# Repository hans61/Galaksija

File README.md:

# Galaksija Plus

I became aware of the "Galaksija" in this forum:

https://forum.classic-computing.de/forum/index.php?thread/27005-nachbau-eines-galaksija-plus-computers/&postID=372260#post372260

I find the Yugoslavian computer from 1983 based on a Z80 very interesting. Especially the idea to give it a SD card afterwards. Especially since it does not use a microcontroller, but implements the SPI interface with a 74LS299.

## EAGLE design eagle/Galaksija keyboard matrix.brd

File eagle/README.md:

# Galaksija keyboard matrix

My attempt to design a PCB for a keyboard of a Galaksija Plus.
Currently it is still untested!

For the first attempt I decided to use 12mm x 12mm styli.
Similar to the buttons here:

https://www.mouser.de/ProductDetail/CUI-Devices/TS13-1212-73-BK-100-D?qs=t7xnP681wgVrw7zKuc8u2g%3D%3D

with keycaps similar to these:

https://www.mouser.de/ProductDetail/Mountain-Switch/101-0110-EV?qs=eB3zOl243QFujTA3cWnhpg%3D%3D

My push buttons are from Aliexpress, something like this:

50PCS b3f-4055 12X1 2x 7,3mm 4PIN dip TACT push button schalter Micro key power tactile switches 12x1 2x 7,3 12*12*7,3 MM Licht touc
https://de.aliexpress.com/item/32853348805.html

https://de.aliexpress.com/item/32852734000.html

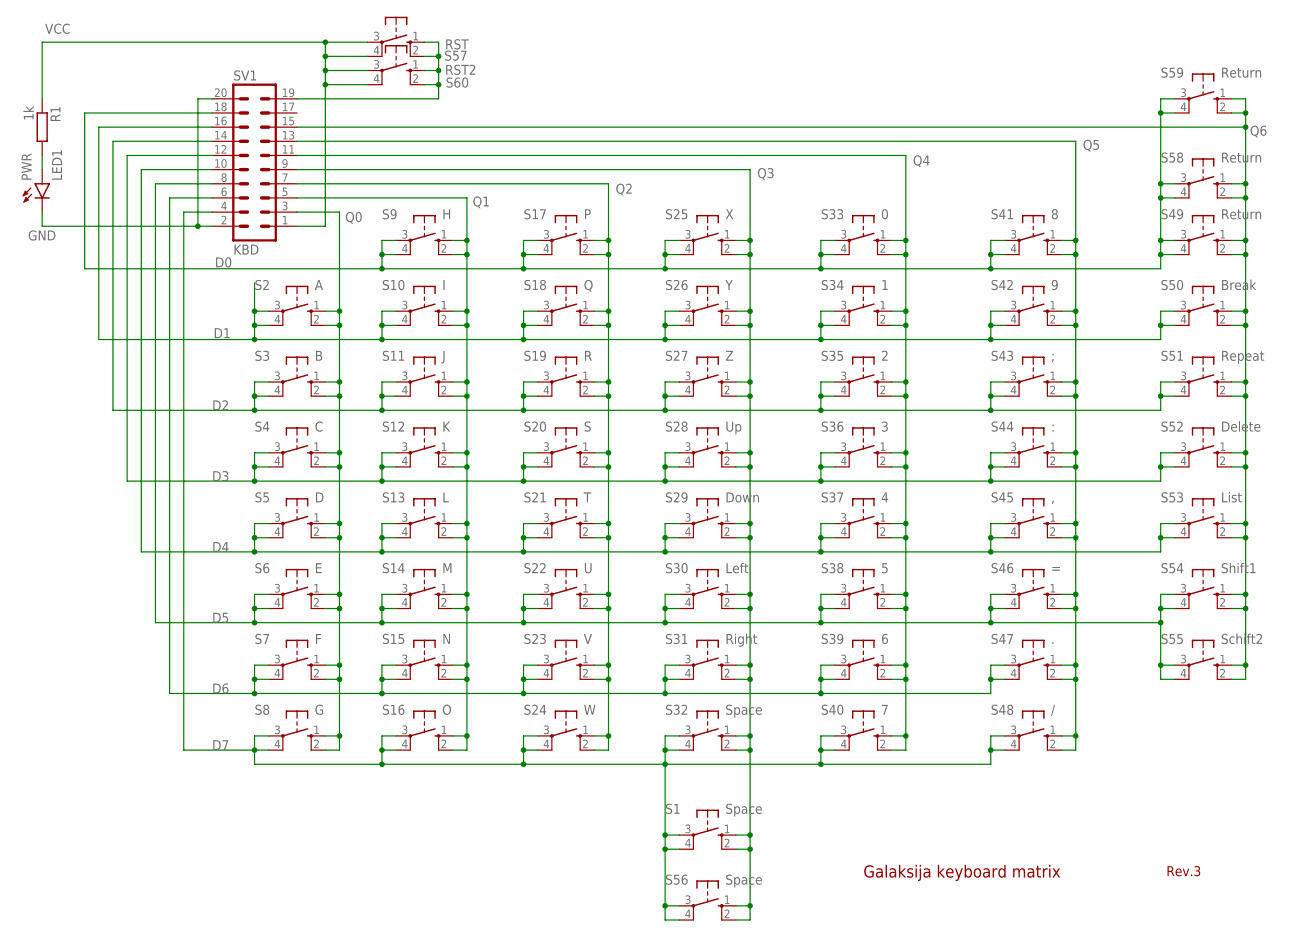
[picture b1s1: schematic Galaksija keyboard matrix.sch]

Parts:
LED1: PWR; LED5MM
R1: 1k; 0207/10
S1, S32, S56: Space; B3F-40XX
S2: A; B3F-40XX
S3: B; B3F-40XX
S4: C; B3F-40XX
S5: D; B3F-40XX
S6: E; B3F-40XX
S7: F; B3F-40XX
S8: G; B3F-40XX
S9: H; B3F-40XX
S10: I; B3F-40XX
S11: J; B3F-40XX
S12: K; B3F-40XX
S13: L; B3F-40XX
S14: M; B3F-40XX
S15: N; B3F-40XX
S16: O; B3F-40XX
S17: P; B3F-40XX
S18: Q; B3F-40XX
S19: R; B3F-40XX
S20: S; B3F-40XX
S21: T; B3F-40XX
S22: U; B3F-40XX
S23: V; B3F-40XX
S24: W; B3F-40XX
S25: X; B3F-40XX
S26: Y; B3F-40XX
S27: Z; B3F-40XX
S28: Up; B3F-40XX
S29: Down; B3F-40XX
S30: Left; B3F-40XX
S31: Right; B3F-40XX
S33: 0; B3F-40XX
S34: 1; B3F-40XX
S35: 2; B3F-40XX
S36: 3; B3F-40XX
S37: 4; B3F-40XX
S38: 5; B3F-40XX
S39: 6; B3F-40XX
S40: 7; B3F-40XX
S41: 8; B3F-40XX
S42: 9; B3F-40XX
S43: ;; B3F-40XX
S44: :; B3F-40XX
S45: ,; B3F-40XX
S46: =; B3F-40XX
S47: .; B3F-40XX
S48: /; B3F-40XX
S49, S58, S59: Return; B3F-40XX
S50: Break; B3F-40XX
S51: Repeat; B3F-40XX
S52: Delete; B3F-40XX
S53: List; B3F-40XX
S54: Shift1; B3F-40XX
S55: Schift2; B3F-40XX
S57: RST; B3F-40XX
S60: RST2; B3F-10XX
SV1: KBD; ML20

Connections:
D0: S9.3, S9.4 (P1), S17.3, S17.4 (P1), S25.3, S25.4 (P1), S33.3, S33.4 (P1), S41.3, S41.4 (P1), S49.3, S49.4 (P1), S58.3, S58.4 (P1), S59.3, S59.4 (P1), SV1.18
D1: S2.3, S2.4 (P1), S10.3, S10.4 (P1), S18.3, S18.4 (P1), S26.3, S26.4 (P1), S34.3, S34.4 (P1), S42.3, S42.4 (P1), S50.3, S50.4 (P1), SV1.16
D2: S3.3, S3.4 (P1), S11.3, S11.4 (P1), S19.3, S19.4 (P1), S27.3, S27.4 (P1), S35.3, S35.4 (P1), S43.3, S43.4 (P1), S51.3, S51.4 (P1), SV1.14
D3: S4.3, S4.4 (P1), S12.3, S12.4 (P1), S20.3, S20.4 (P1), S28.3, S28.4 (P1), S36.3, S36.4 (P1), S44.3, S44.4 (P1), S52.3, S52.4 (P1), SV1.12
D4: S5.3, S5.4 (P1), S13.3, S13.4 (P1), S21.3, S21.4 (P1), S29.3, S29.4 (P1), S37.3, S37.4 (P1), S45.3, S45.4 (P1), S53.3, S53.4 (P1), SV1.10
D5: S6.3, S6.4 (P1), S14.3, S14.4 (P1), S22.3, S22.4 (P1), S30.3, S30.4 (P1), S38.3, S38.4 (P1), S46.3, S46.4 (P1), S54.3, S54.4 (P1), S55.3, S55.4 (P1), SV1.8
D6: S7.3, S7.4 (P1), S15.3, S15.4 (P1), S23.3, S23.4 (P1), S31.3, S31.4 (P1), S39.3, S39.4 (P1), S47.3, S47.4 (P1), SV1.6
D7: S1.3, S1.4 (P1), S8.3, S8.4 (P1), S16.3, S16.4 (P1), S24.3, S24.4 (P1), S32.3, S32.4 (P1), S40.3, S40.4 (P1), S48.3, S48.4 (P1), S56.3, S56.4 (P1), SV1.4
GND: LED1.K (C), SV1.2, SV1.20
unnamed: LED1.A, R1.2
Q0: S2.1 (S), S2.2 (S1), S3.1 (S), S3.2 (S1), S4.1 (S), S4.2 (S1), S5.1 (S), S5.2 (S1), S6.1 (S), S6.2 (S1), S7.1 (S), S7.2 (S1), S8.1 (S), S8.2 (S1), SV1.3
Q1: S9.1 (S), S9.2 (S1), S10.1 (S), S10.2 (S1), S11.1 (S), S11.2 (S1), S12.1 (S), S12.2 (S1), S13.1 (S), S13.2 (S1), S14.1 (S), S14.2 (S1), S15.1 (S), S15.2 (S1), S16.1 (S), S16.2 (S1), SV1.5
Q2: S17.1 (S), S17.2 (S1), S18.1 (S), S18.2 (S1), S19.1 (S), S19.2 (S1), S20.1 (S), S20.2 (S1), S21.1 (S), S21.2 (S1), S22.1 (S), S22.2 (S1), S23.1 (S), S23.2 (S1), S24.1 (S), S24.2 (S1), SV1.7
Q3: S1.1 (S), S1.2 (S1), S25.1 (S), S25.2 (S1), S26.1 (S), S26.2 (S1), S27.1 (S), S27.2 (S1), S28.1 (S), S28.2 (S1), S29.1 (S), S29.2 (S1), S30.1 (S), S30.2 (S1), S31.1 (S), S31.2 (S1), S32.1 (S), S32.2 (S1), S56.1 (S), S56.2 (S1), SV1.9
Q4: S33.1 (S), S33.2 (S1), S34.1 (S), S34.2 (S1), S35.1 (S), S35.2 (S1), S36.1 (S), S36.2 (S1), S37.1 (S), S37.2 (S1), S38.1 (S), S38.2 (S1), S39.1 (S), S39.2 (S1), S40.1 (S), S40.2 (S1), SV1.11
Q5: S41.1 (S), S41.2 (S1), S42.1 (S), S42.2 (S1), S43.1 (S), S43.2 (S1), S44.1 (S), S44.2 (S1), S45.1 (S), S45.2 (S1), S46.1 (S), S46.2 (S1), S47.1 (S), S47.2 (S1), S48.1 (S), S48.2 (S1), SV1.13
Q6: S49.1 (S), S49.2 (S1), S50.1 (S), S50.2 (S1), S51.1 (S), S51.2 (S1), S52.1 (S), S52.2 (S1), S53.1 (S), S53.2 (S1), S54.1 (S), S54.2 (S1), S55.1 (S), S55.2 (S1), S58.1 (S), S58.2 (S1), S59.1 (S), S59.2 (S1), SV1.15
RST: S57.1 (S), S57.2 (S1), S60.1 (S), S60.2 (S1), SV1.19
VCC: R1.1, S57.3, S57.4 (P1), S60.3, S60.4 (P1), SV1.1

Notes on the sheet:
Galaksija keyboard matrix
Rev.3

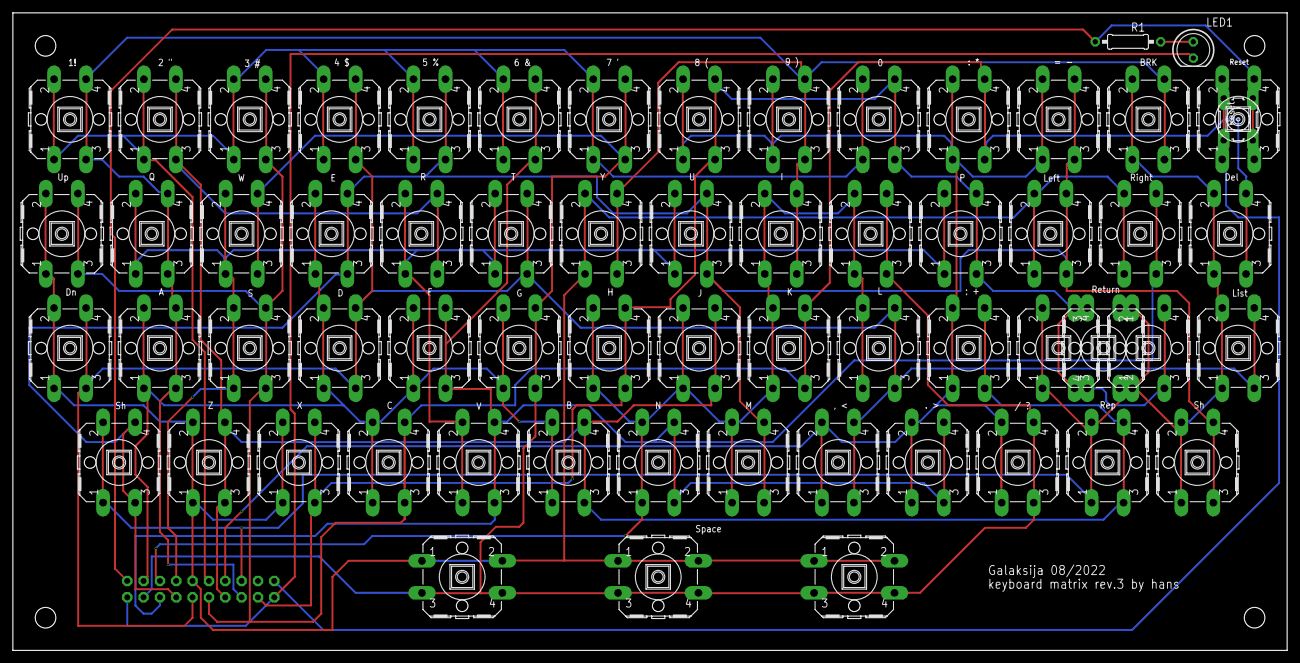
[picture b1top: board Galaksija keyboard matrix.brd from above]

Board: 2 copper layers, 198.1 x 99.1 mm, 63 parts (1 on the bottom side), 19 nets.

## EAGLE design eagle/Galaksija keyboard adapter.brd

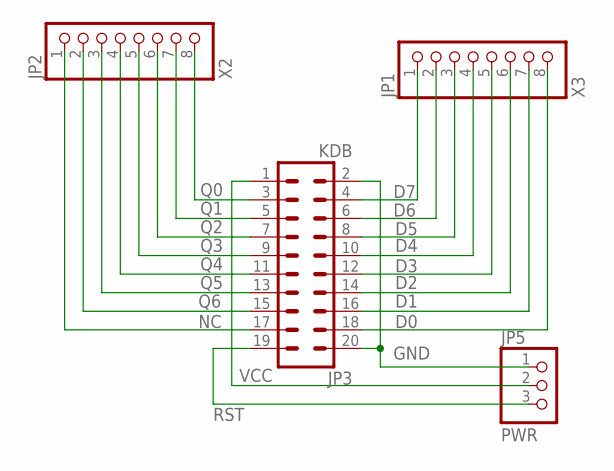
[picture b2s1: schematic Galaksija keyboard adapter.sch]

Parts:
JP1: X3; 1X08
JP2: X2; 1X08
JP3: KDB; ML20
JP5: PWR; 1X03

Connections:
D0: JP1.8, JP3.18
D1: JP1.7, JP3.16
D2: JP1.6, JP3.14
D3: JP1.5, JP3.12
D4: JP1.4, JP3.10
D5: JP1.3, JP3.8
D6: JP1.2, JP3.6
D7: JP1.1, JP3.4
GND: JP3.2, JP3.20, JP5.1
NC: JP2.1, JP3.17
Q0: JP2.8, JP3.3
Q1: JP2.7, JP3.5
Q2: JP2.6, JP3.7
Q3: JP2.5, JP3.9
Q4: JP2.4, JP3.11
Q5: JP2.3, JP3.13
Q6: JP2.2, JP3.15
RST: JP3.19, JP5.3
VCC: JP3.1, JP5.2

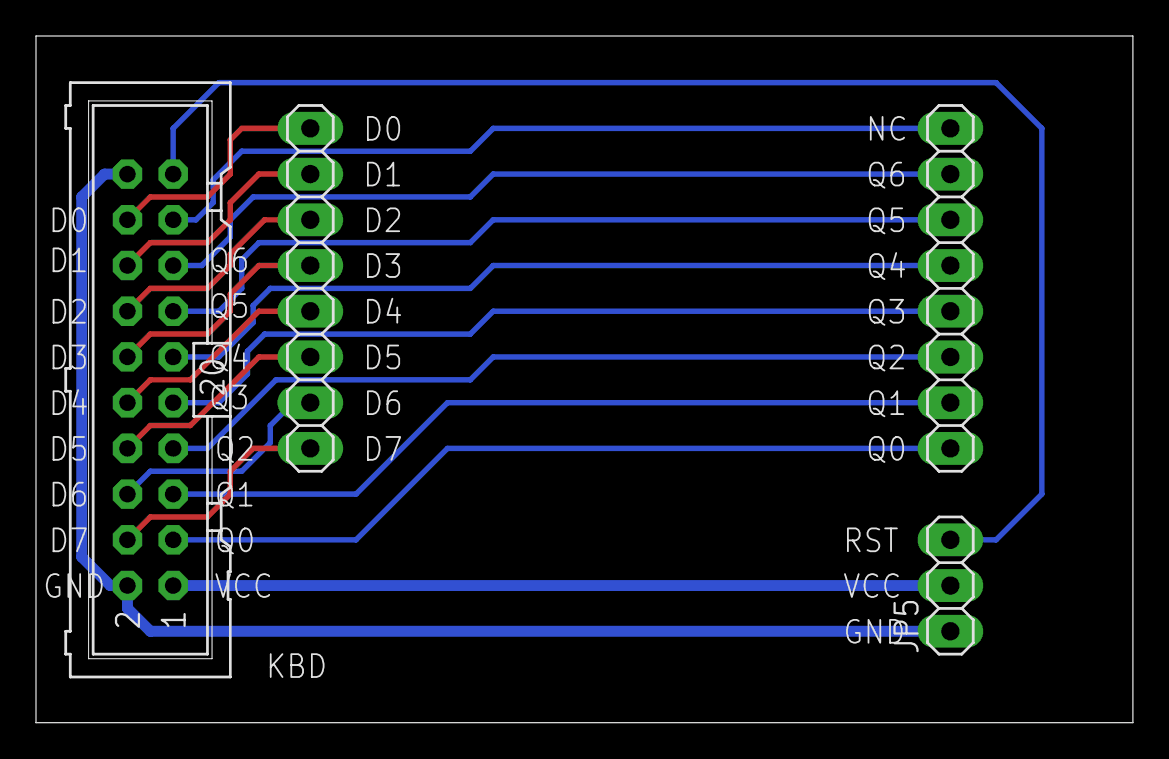
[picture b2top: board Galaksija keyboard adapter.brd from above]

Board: 2 copper layers, 60.9 x 38.2 mm, 4 parts (0 on the bottom side), 19 nets.

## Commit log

2022-08-05 First version of the keyboard
2022-08-08 New version Rev.2
2022-08-10 Keyboard connector pinout added
2022-08-21 added keyboard rom de
2022-08-22 Added keyboard layout EN (untested)
2022-08-24 first version add keys
2022-08-27 labeling for 10*10mm keys
2022-08-28 Rev3 narrower version with modified ENTER key
2022-08-29 finished keyboard revision 3
2022-08-29 correction
2022-09-01 update keyboard lable
2023-02-25 cleaning
2023-02-25 change german keys
2023-02-25 Shift-Break, Shift-Del
2023-02-25 cleaning keyboard files
2023-02-25 update readmecleaning keyboard files
2023-02-25 update picture
2023-02-26 PS2 Adapter ROM Anleitung
